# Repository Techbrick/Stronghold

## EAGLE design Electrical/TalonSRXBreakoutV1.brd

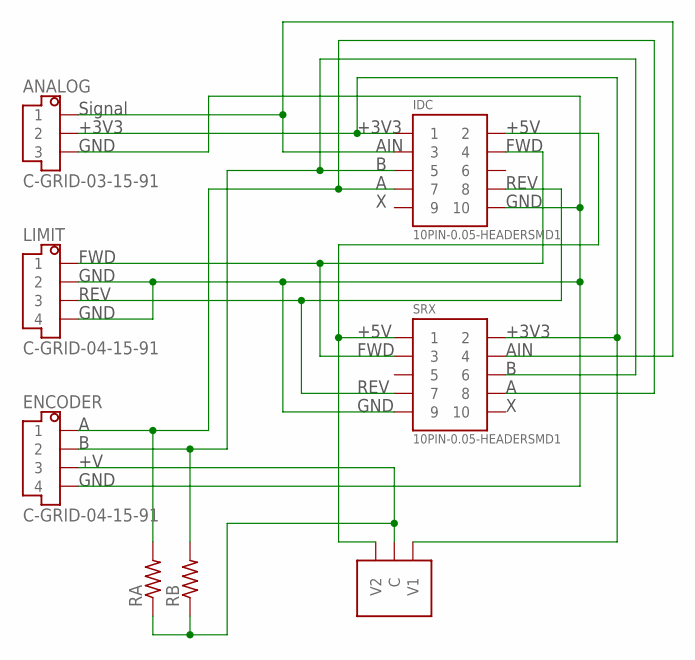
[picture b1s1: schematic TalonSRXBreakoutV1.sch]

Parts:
ANALOG: C-GRID-03-15-91; 15-91-03
ENCODER: C-GRID-04-15-91; 15-91-04
IDC: 10PIN-0.05-HEADERSMD1; 1.27-10PIN
LIMIT: C-GRID-04-15-91; 15-91-04
RA: R-US_R0805; R0805
RB: R-US_R0805; R0805
SRX: 10PIN-0.05-HEADERSMD1; 1.27-10PIN
U$1: 3PIN-RA-VSELECT; 2.54-3PIN-SMD-RA

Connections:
unnamed: ANALOG.1, IDC.P3 (3), SRX.P4 (4)
unnamed: ANALOG.3, ENCODER.4, IDC.P10 (10), LIMIT.2, LIMIT.4, SRX.P9 (9)
unnamed: ANALOG.2, IDC.P1 (1), SRX.P2 (2), U$1.P1 (V1)
unnamed: IDC.P8 (8), LIMIT.3, SRX.P7 (7)
unnamed: IDC.P4 (4), LIMIT.1, SRX.P3 (3)
unnamed: ENCODER.1, IDC.P7 (7), RA.2, SRX.P8 (8)
unnamed: ENCODER.2, IDC.P5 (5), RB.2, SRX.P6 (6)
unnamed: IDC.P2 (2), SRX.P1 (1), U$1.P3 (V2)
unnamed: ENCODER.3, RA.1, RB.1, U$1.P2 (C)

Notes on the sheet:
Signal
+3V3
GND
FWD
REV
+5V
AIN

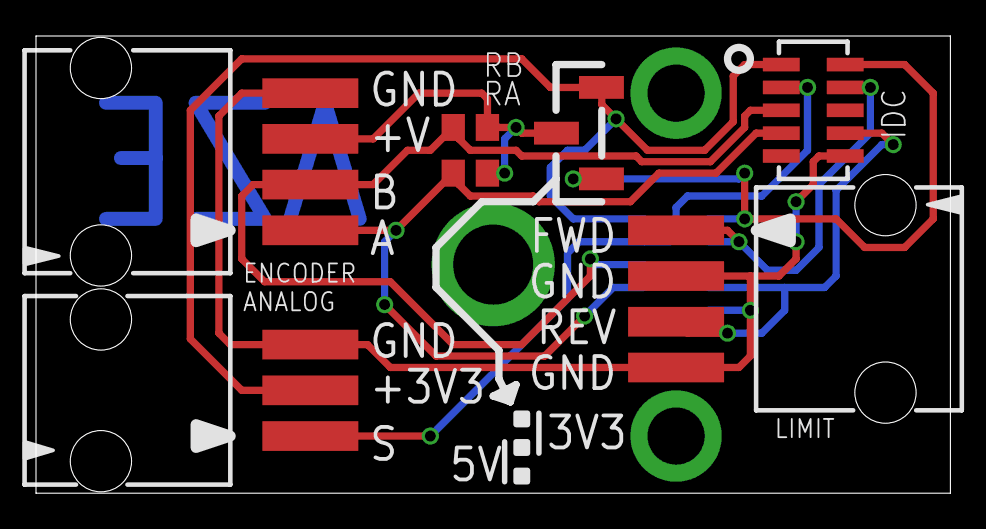
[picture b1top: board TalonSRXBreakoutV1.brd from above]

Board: 2 copper layers, 50.8 x 25.4 mm, 8 parts (1 on the bottom side), 9 nets.

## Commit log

2016-01-10 Update LED_Strip.ino
    LED Code from 2015. To be updated.
2016-01-25 Create Stronghold
2016-01-25 Create Constants.cpp
    Made all values zero because I don't actually know the values yet
2016-01-28 Moved everything to ./
2016-01-30 Moved files
2016-01-30 Added .gitignore
2016-01-30 Deleted backwards switch class
2016-01-30 Added Subsys reqs
2016-02-02 Added test.txt
2016-02-03 Added aimer class.
2016-02-05 Files sent off to OSHPark for manufacture
2016-02-06 Very Simple 10 connector locking clip that can be plugged into the roboRio.
2016-02-06 Removed test.txt
2016-02-06 Taking files from Test_Tank_Drive
2016-02-06 Added better Robot.cpp
2016-02-06 Added constructors to DriveTrain
2016-02-08 Added game manual
2016-02-09 Tracker jar.
2016-02-11 Added cantalons to DriveTrain class with enable/disable functions
2016-02-11 Enable/disable driveTrain in operator control function
2016-02-11 Combined Constants.cpp and Constants.h into Constants.h
2016-02-11 Fixed constants
2016-02-13 DriveTrain class code from branch simpleTest
2016-02-13 Added DriveTrain class in and Shooter class, plus some constants
2016-02-13 Added max speed for pulling the ball into the shooter
2016-02-13 updated to call to Position class's Update function to a non-static call
2016-02-15 Added navx-mxp header and object file to navx-mxp folder
2016-02-15 Added in tower position coordinates in Constants.h
2016-02-15 Modified make main recipe in Makefile to link navx-mxp files
2016-02-15 Fixes to position class
2016-02-15 Removed an include of NetworkTables.h in Aimer.h, because it's already included in WPILib.h
2016-02-17 Better version yall
2016-02-17 intial commit of arm class
2016-02-19 New Tracker things.
2016-02-20 Added files via upload
2016-02-20 Switched make open to use vim
2016-02-20 Added shooter minimum and maximum angle to Constants.h
2016-02-20 Various minor fixes to Shooter class
2016-02-20 Fixed errors from merging
2016-02-23 Added in pin defs to Constants.h (except joystick buttons)
2016-02-23 Added TODO to DriveTrain
2016-02-23 Removed TestThread and fixed shooter logic'
2016-02-23 Random fixes
2016-02-23 Removed Pot from Shooter class
2016-02-24 Create Robot Test Mode Code
2016-02-24 Update Robot Test Mode Code
2016-02-24 Finished Tracker.jar
2016-02-24 Updated to match actual robot pins
2016-02-24 Added Test function
2016-02-24 Added Masters and followers
2016-02-24 Changed DriveTrain constructor
2016-02-24 Fixed shooter.SetAngle(float angle)
2016-03-02 Compile with warnings
2016-03-02 Fixed order of init's in Robot.cpp
2016-03-02 Fixed the rest of the reorder errors and the uninit'd variable error
2016-03-05 Added debugging code
2016-03-05 test code that works
2016-03-07 Fixed testing code
2016-03-09 Fixed issue with Camera code that was crashing the code: put it in the RobotInit method
2016-03-12 Removed old test code
2016-03-16 Added pin defs for arm
2016-03-16 Changed DriveTrain::TurnToAngle(float) to PI loop
2016-03-16 Added calibration capabilities for Shooter::SetAngle()
2016-03-20 These are the changes and fixes made during the Harford Tech Highschool competition on Saturday. They compile with no errors, and seem to have solved many of the problems we were experiencing through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
2016-03-20 .gitignore now ignores swap files from code editors (esp. vim)
2016-03-20 Formatting fixes in Robot.cpp
2016-03-20 Added TODO with question for TJ (important!)
2016-03-20 Added a .gitattributes file
    This should help GitHub linguist know not to count the CAD files in Electrical/ as our lines of code.
2016-03-20 Completed paths in .gitattributes
2016-03-23 Tuneable drivetrain pid loop
2016-03-24 Fixing auto code
2016-03-31 adding dotstar (apa102) test code
2016-03-31 PID Testing / CANTalon Speed Control
2016-03-31 Reversed left talon
    Properly reversed the Drive Train's left Talon
2016-03-31 3/31 Changes Made - Uploading to test PID loop
2016-03-31 premerge
2016-04-01 Commit first version of working LED code t obe used on robot.
2016-04-06 fixes
2016-04-06 Shooter kicker adjustments
2016-04-06 So shooter won't jam
2016-04-06 Made use TankdDriveSpeed
2016-04-06 PID Tuning
2016-04-06 Made kicker spin longer
2016-04-06 Disabled PID turning in main code
2016-04-06 Remove I term from right Talon PID Loop, reverse motors
2016-04-06 Nearly working PID turning loop
2016-04-07 stuff:
2016-04-07 Shooter Angle Stuff
2016-04-07 Comment out l1 code
2016-04-07 tune shooter pot
2016-04-07 tuning pot values
2016-04-07 Shooter angle stuff changed (hopefully fixed) and smartdashboard stuff changed
2016-04-07 Shooter angle stuff changed (hopefully fixed but idk tbh)
2016-04-07 Constants distances array deleted - it wasn't used and it cluttered up our constants file with 420 lines
2016-04-07 Fixed merging issue with Position Class
2016-04-07 Remove test code for servos
2016-04-07 Auto code changes
2016-04-07 Adjusted pot values
2016-04-07 Position mode aim code
2016-04-08 something
2016-04-08 Merging from usb-remote
2016-04-08 Added a pid TankDriveStraight method to DriveTrain
2016-09-21 Shooter Changes
    Shooter uses accelerometer to determine angle for BoB. SetAngle still uses the pot though, so that needs to be changed
2016-09-21 Set Angle Fixed
    Shooter::setAngleAccelerometer was written and should work with the exception of potentially flipping a negative
    Comments were added to Shooter::setAngle to let you know where you might need to flip a negative should you decide to use the pot instead of the accelerometer
